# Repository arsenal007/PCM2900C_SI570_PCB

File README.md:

# PCM2900C Si570
KiCAD PCB Project of SDR processor board, based on PCM2900C and Si570

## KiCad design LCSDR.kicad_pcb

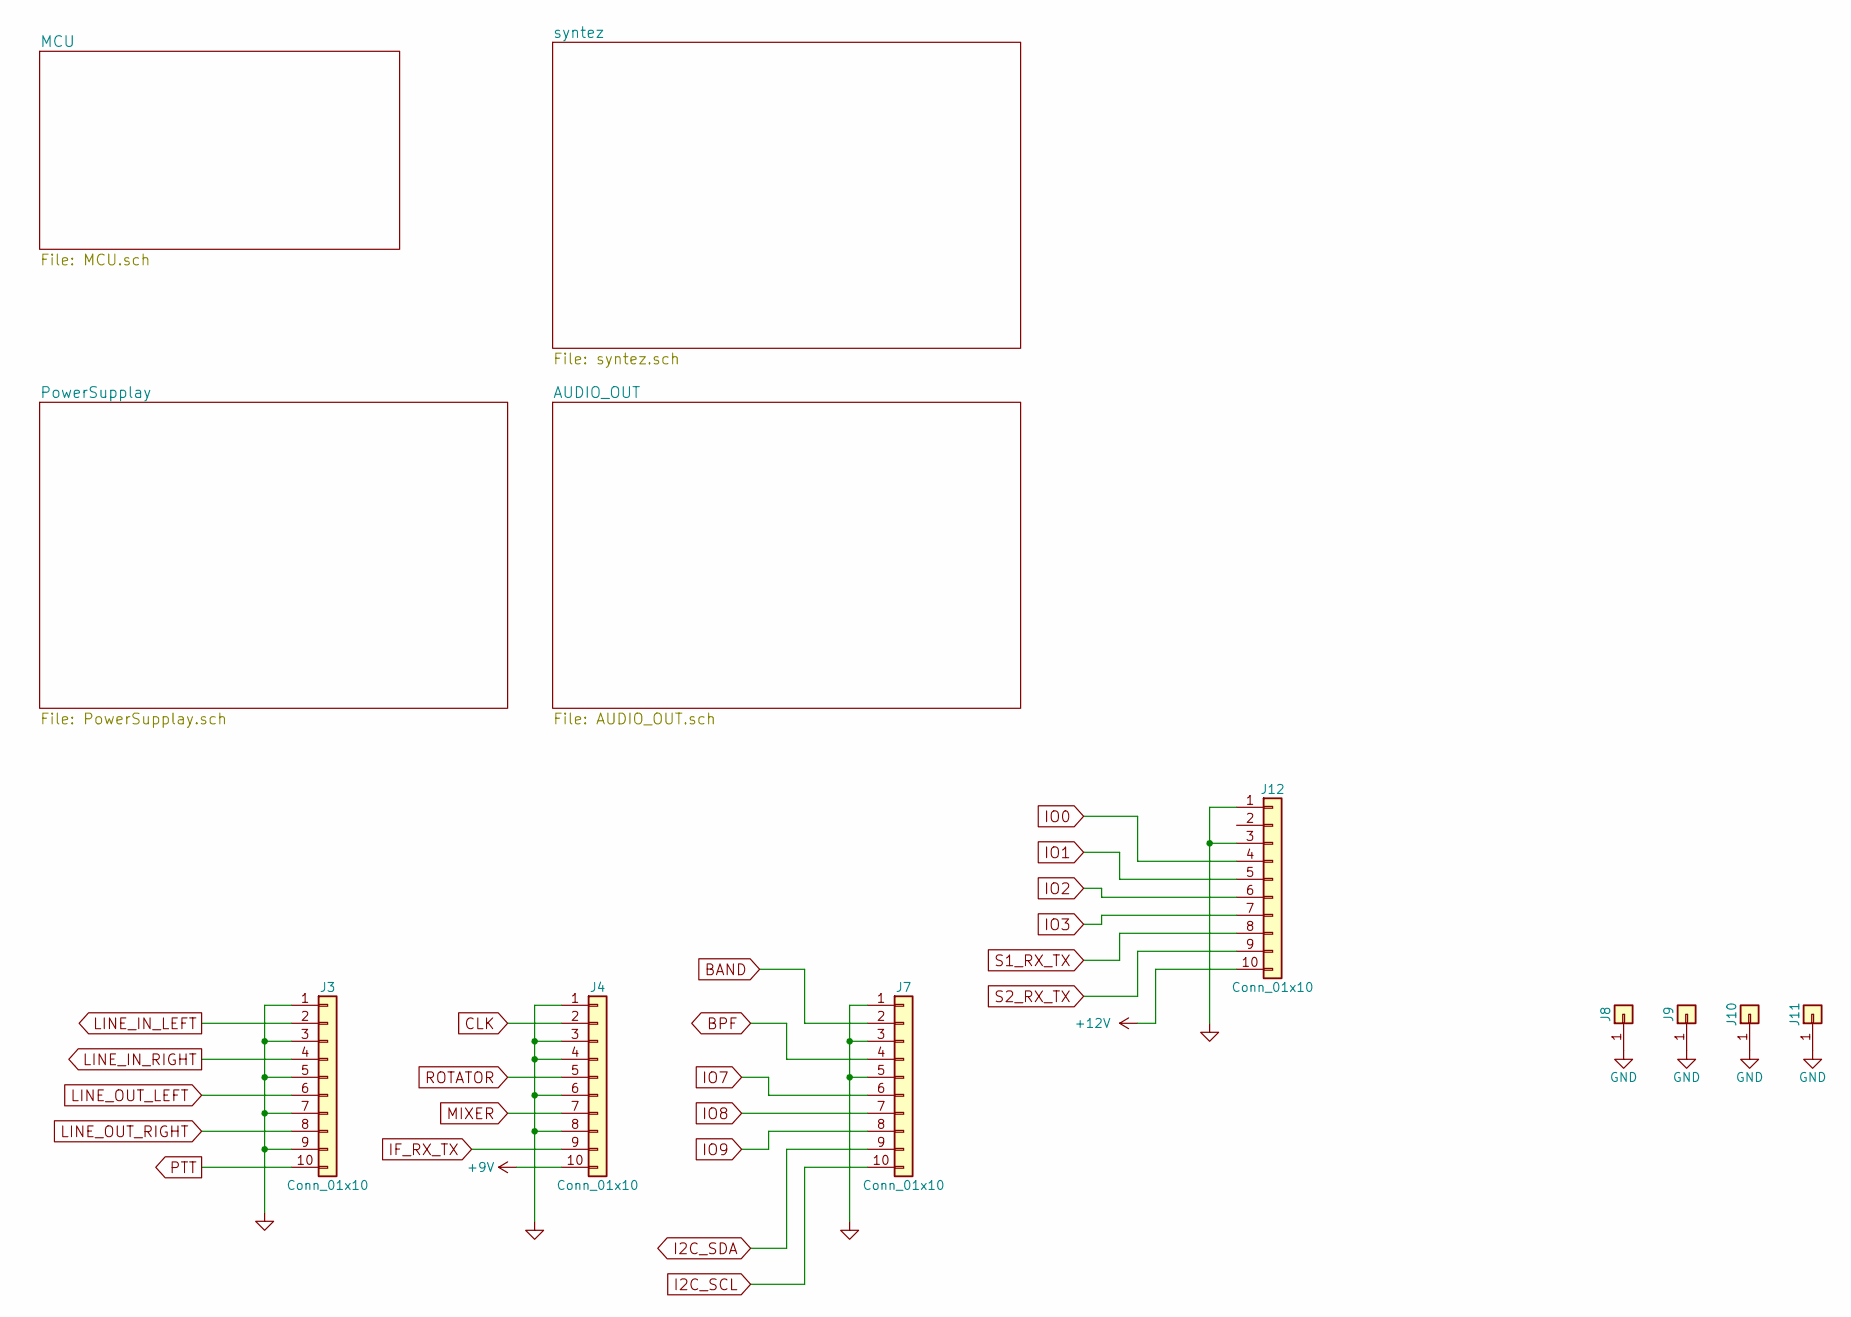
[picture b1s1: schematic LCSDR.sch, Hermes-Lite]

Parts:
J3, J4, J7, J12: Conn_01x10; Pin_Header_Straight_1x10_Pitch2.54mm
J8, J9, J10, J11: Conn_01x01; MountingHole_3.2mm_M3_DIN965_Pad

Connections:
+9V: J4.10; also elsewhere on the board
+12V: J12.10; also elsewhere on the board
BAND: J7.2; also elsewhere on the board
CLK: J4.2; also elsewhere on the board
GND: J3.1, J3.3, J3.5, J3.7, J3.9, J4.1, J4.3, J4.4, J4.6, J4.8, J7.1, J7.3, J7.5, J8.1, J9.1, J10.1, J11.1, J12.1, J12.3; also elsewhere on the board
I2C_SCL: J7.10; also elsewhere on the board
I2C_SDA: J7.9; also elsewhere on the board
IF_RX_TX: J4.9; also elsewhere on the board
IO0: J12.4; also elsewhere on the board
IO1: J12.5; also elsewhere on the board
IO2: J12.6; also elsewhere on the board
IO3: J12.7; also elsewhere on the board
IO7: J7.6; also elsewhere on the board
IO8: J7.7; also elsewhere on the board
IO9: J7.8; also elsewhere on the board
LINE_IN_LEFT: J3.2; also elsewhere on the board
LINE_IN_RIGHT: J3.4; also elsewhere on the board
LINE_OUT_LEFT: J3.6; also elsewhere on the board
LINE_OUT_RIGHT: J3.8; also elsewhere on the board
MIXER: J4.7; also elsewhere on the board
ROTATOR: J4.5; also elsewhere on the board
S1_RX_TX: J12.8; also elsewhere on the board
S2_RX_TX: J12.9; also elsewhere on the board

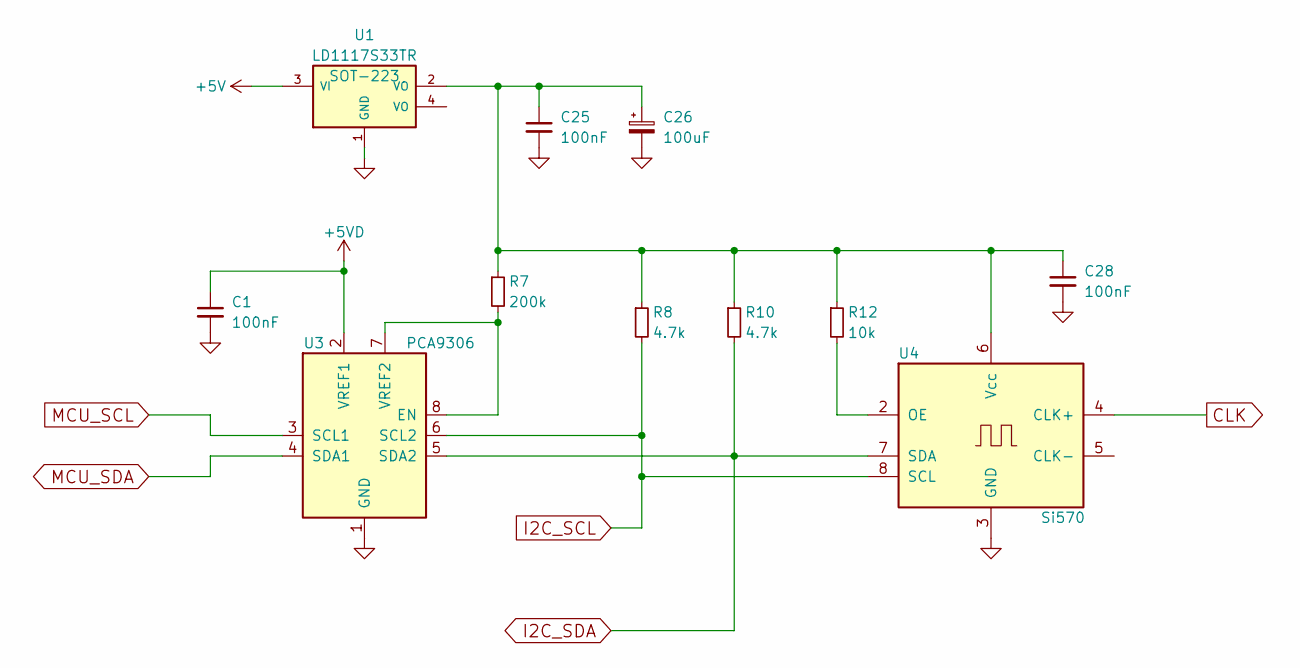
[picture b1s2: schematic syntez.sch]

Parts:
C1, C25, C28: 100nF; C_1206_0603
C26: 100uF; CP_Radial_D6.3mm_P2.50mm
R7: 200k; R_1206_0603
R8, R10: 4.7k; R_1206_0603
R12: 10k; R_1206_0603
U1: LD1117S33TR; SOT-223
U3: PCA9306; SSOP-8_2.95x2.8mm_Pitch0.65mm
U4: Si570; Oscillator_SMD_SI570_SI571_Standard

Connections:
+5V: U1.3 (VI); also elsewhere on the board
+5VD: C1.1, U3.2 (VREF1); also elsewhere on the board
CLK: U4.4 (CLK+); also elsewhere on the board
GND: C1.2, C25.2, C26.2, C28.2, U1.1 (GND), U3.1 (GND), U4.3 (GND); also elsewhere on the board
I2C_SCL: R8.2, U3.6 (SCL2), U4.8 (SCL); also elsewhere on the board
I2C_SDA: R10.2, U3.5 (SDA2), U4.7 (SDA); also elsewhere on the board
MCU_SCL: U3.3 (SCL1); also elsewhere on the board
MCU_SDA: U3.4 (SDA1); also elsewhere on the board
unnamed: C25.1, C26.1, C28.1, R7.1, R8.1, R10.1, R12.1, U1.2 (VO), U4.6 (Vcc)
unnamed: R7.2, U3.7 (VREF2), U3.8 (EN)
unnamed: R12.2, U4.2 (OE)

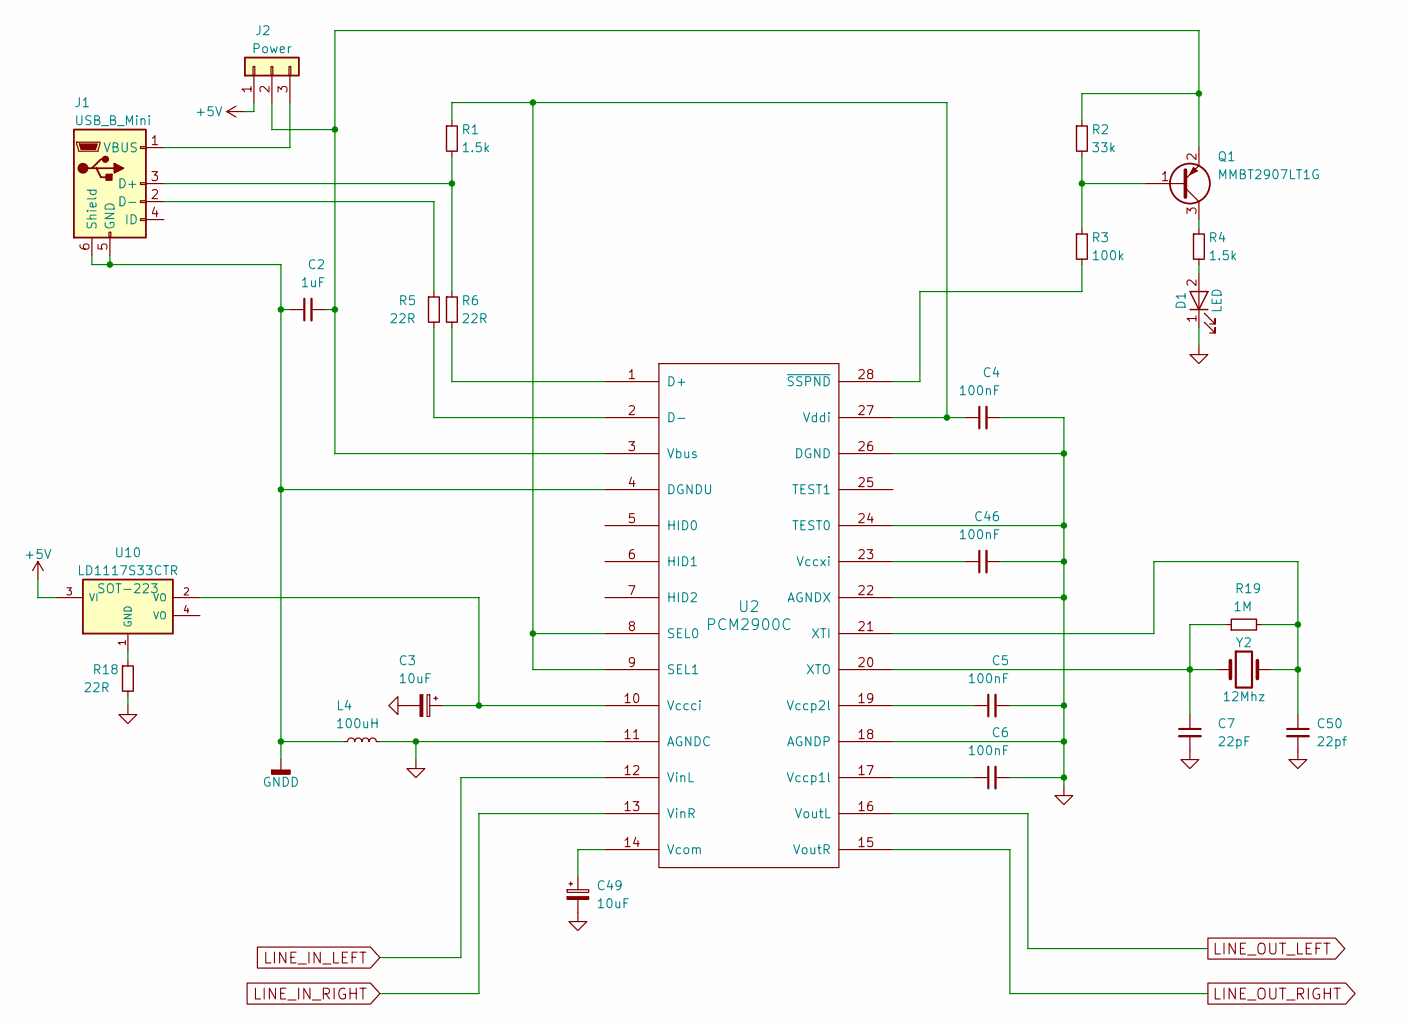
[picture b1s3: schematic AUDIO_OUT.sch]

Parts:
C2: 1uF; C_1206_0603
C3, C49: 10uF; CP_Radial_D5.0mm_P2.00mm
C4, C5, C6, C46: 100nF; C_1206_0603
C7: 22pF; C_1206_0603
C50: 22pf; C_1206_0603
D1: LED; LED_0603_HandSoldering
J1: USB_B_Mini; USB_Mini-B
J2: Power; Pin_Header_Straight_1x03_Pitch2.54mm
L4: 100uH; Choke_Horizontal_RM10mm
Q1: MMBT2907LT1G; SOT-23
R1, R4: 1.5k; R_1206_0603
R2: 33k; R_1206_0603
R3: 100k; R_1206_0603
R5, R6, R18: 22R; R_1206_0603
R19: 1M; R_1206_0603
U2: PCM2900C; SSOP-28_5.3x10.2mm_Pitch0.65mm
U10: LD1117S33CTR; SOT-223
Y2: 12Mhz; Crystal_HC49-U_Vertical

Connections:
+5V: J2.1, U10.3 (VI); also elsewhere on the board
GND: C3.2, C4.2, C5.2, C6.2, C7.2, C46.2, C49.2, C50.2, D1.1 (K), L4.2, R18.2, U2.11 (AGNDC), U2.18 (AGNDP), U2.22 (AGNDX), U2.24 (TEST0), U2.26 (DGND); also elsewhere on the board
GNDD: C2.1, J1.5 (GND), J1.6 (Shield), L4.1, U2.4 (DGNDU)
LINE_IN_LEFT: U2.12 (VinL); also elsewhere on the board
LINE_IN_RIGHT: U2.13 (VinR); also elsewhere on the board
LINE_OUT_LEFT: U2.16 (VoutL); also elsewhere on the board
LINE_OUT_RIGHT: U2.15 (VoutR); also elsewhere on the board
unnamed: C2.2, J2.2, Q1.2 (E), R2.1, U2.3 (Vbus)
unnamed: C3.1, U2.10 (Vccci), U10.2 (VO)
unnamed: C4.1, R1.1, U2.8 (SEL0), U2.9 (SEL1), U2.27 (Vddi)
unnamed: C5.1, U2.19 (Vccp2l)
unnamed: C6.1, U2.17 (Vccp1l)
unnamed: C7.1, R19.1, U2.20 (XTO), Y2.1
unnamed: C46.1, U2.23 (Vccxi)
unnamed: C49.1, U2.14 (Vcom)
unnamed: C50.1, R19.2, U2.21 (XTI), Y2.2
unnamed: D1.2 (A), R4.2
unnamed: J1.1 (VBUS), J2.3
unnamed: J1.2 (D-), R5.1
unnamed: J1.3 (D+), R1.2, R6.1
unnamed: Q1.1 (B), R2.2, R3.1
unnamed: Q1.3 (C), R4.1
unnamed: R3.2, U2.28 (~SSPND)
unnamed: R5.2, U2.2 (D-)
unnamed: R6.2, U2.1 (D+)
unnamed: R18.1, U10.1 (GND)

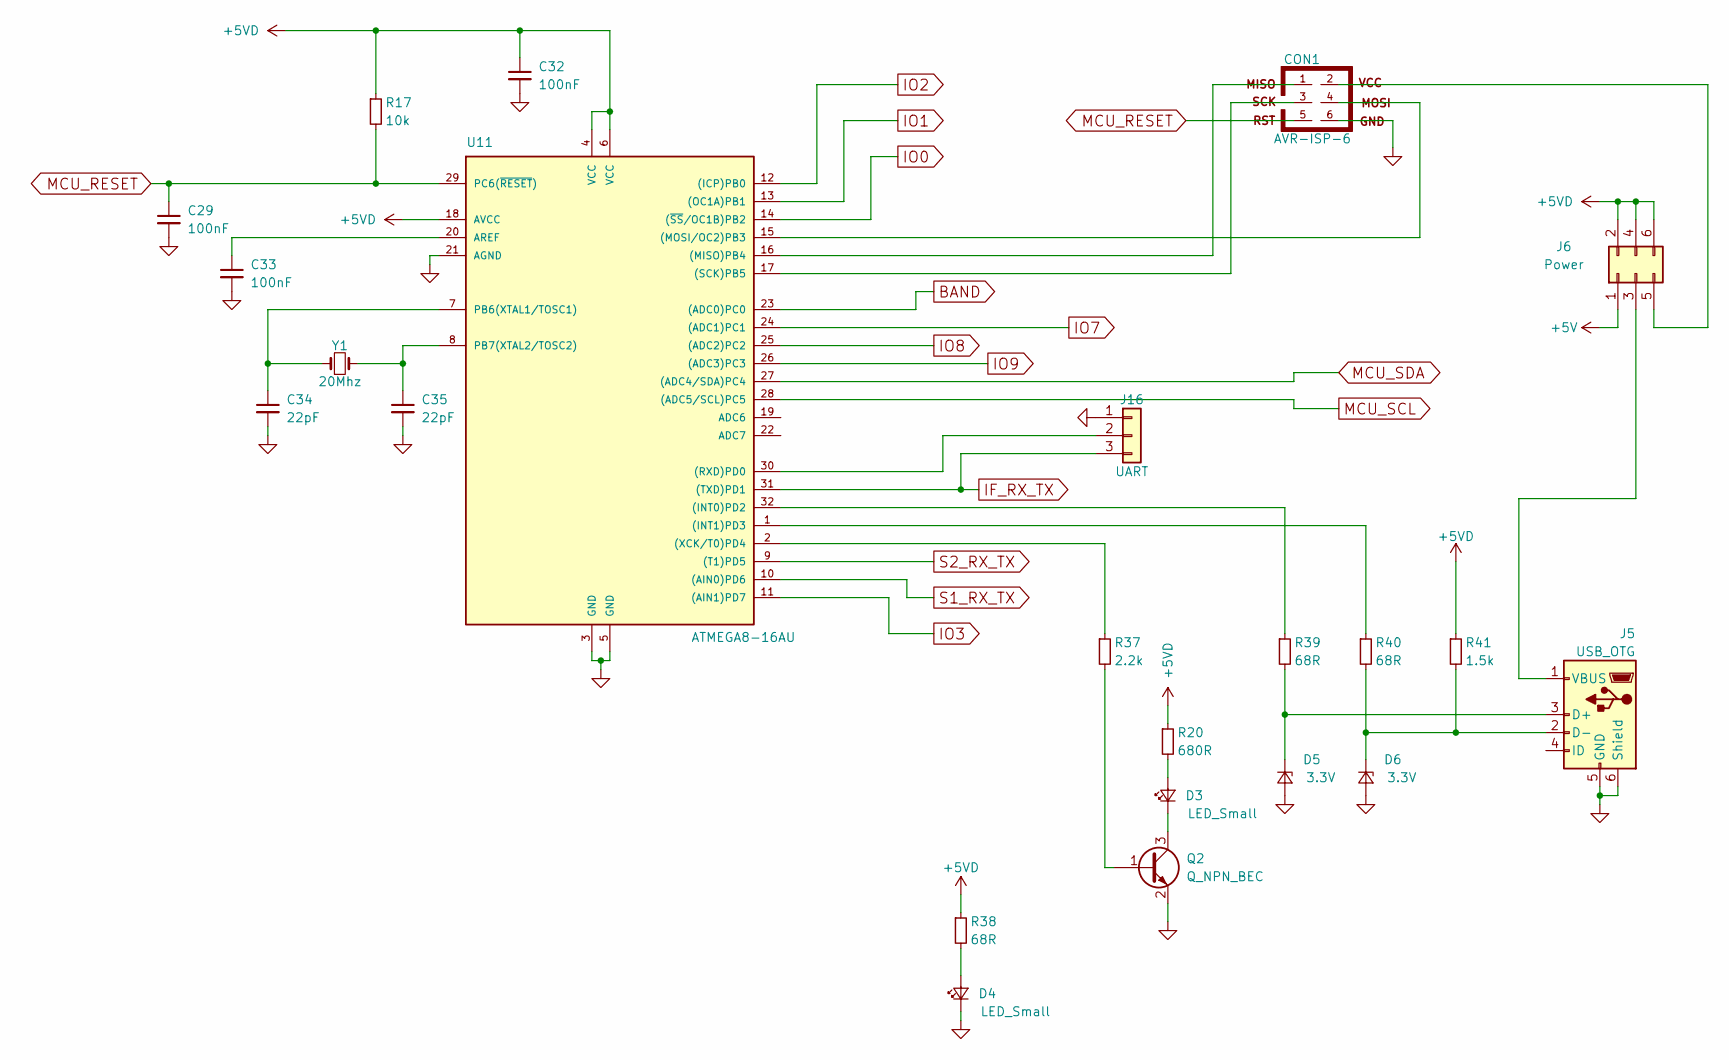
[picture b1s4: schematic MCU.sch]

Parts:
C29, C32, C33: 100nF; C_1206_0603
C34, C35: 22pF; C_1206_0603
CON1: AVR-ISP-6; Pin_Header_Straight_2x03_Pitch2.54mm
D3, D4: LED_Small; LED_0603_HandSoldering
D5, D6: 3.3V; D_MiniMELF
J5: USB_OTG; USB_Mini-B
J6: Power; Pin_Header_Straight_2x03_Pitch2.54mm
J16: UART; Pin_Header_Straight_1x03_Pitch2.54mm
Q2: Q_NPN_BEC; SOT-23
R17: 10k; R_1206_0603
R20: 680R; R_1206_0603
R37: 2.2k; R_1206_0603
R38, R39, R40: 68R; R_1206_0603
R41: 1.5k; R_1206_0603
U11: ATMEGA8-16AU; TQFP-32_7x7mm_Pitch0.8mm
Y1: 20Mhz; Crystal_HC49-U_Vertical

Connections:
+5V: J6.1; also elsewhere on the board
+5VD: C32.1, J6.2, J6.4, J6.6, R17.1, R20.1, R38.1, R41.1, U11.4 (VCC), U11.6 (VCC), U11.18 (AVCC); also elsewhere on the board
BAND: U11.23 ((ADC0)PC0); also elsewhere on the board
GND: C29.2, C32.2, C33.2, C34.2, C35.2, CON1.6, D4.1 (K), D5.2 (A), D6.2 (A), J5.5 (GND), J5.6 (Shield), J16.1, Q2.2 (E), U11.3 (GND), U11.5 (GND), U11.21 (AGND); also elsewhere on the board
IF_RX_TX: J16.3, U11.31 ((TXD)PD1); also elsewhere on the board
IO0: U11.14 ((~SS~/OC1B)PB2); also elsewhere on the board
IO1: U11.13 ((OC1A)PB1); also elsewhere on the board
IO2: U11.12 ((ICP)PB0); also elsewhere on the board
IO3: U11.11 ((AIN1)PD7); also elsewhere on the board
IO7: U11.24 ((ADC1)PC1); also elsewhere on the board
IO8: U11.25 ((ADC2)PC2); also elsewhere on the board
IO9: U11.26 ((ADC3)PC3); also elsewhere on the board
MCU_RESET: C29.1, CON1.5, R17.2, U11.29 (PC6(~RESET~))
MCU_SCL: U11.28 ((ADC5/SCL)PC5); also elsewhere on the board
MCU_SDA: U11.27 ((ADC4/SDA)PC4); also elsewhere on the board
unnamed: C33.1, U11.20 (AREF)
unnamed: C34.1, U11.7 (PB6(XTAL1/TOSC1)), Y1.1
unnamed: C35.1, U11.8 (PB7(XTAL2/TOSC2)), Y1.2
unnamed: CON1.1, U11.16 ((MISO)PB4)
unnamed: CON1.2, J6.5
unnamed: CON1.3, U11.17 ((SCK)PB5)
unnamed: CON1.4, U11.15 ((MOSI/OC2)PB3)
unnamed: D3.1 (K), Q2.3 (C)
unnamed: D3.2 (A), R20.2
unnamed: D4.2 (A), R38.2
unnamed: D5.1 (K), J5.3 (D+), R39.2
unnamed: D6.1 (K), J5.2 (D-), R40.2, R41.2
unnamed: J5.1 (VBUS), J6.3
unnamed: J16.2, U11.30 ((RXD)PD0)
unnamed: Q2.1 (B), R37.2
unnamed: R37.1, U11.2 ((XCK/T0)PD4)
unnamed: R39.1, U11.32 ((INT0)PD2)
unnamed: R40.1, U11.1 ((INT1)PD3)
S1_RX_TX: U11.10 ((AIN0)PD6); also elsewhere on the board
S2_RX_TX: U11.9 ((T1)PD5); also elsewhere on the board

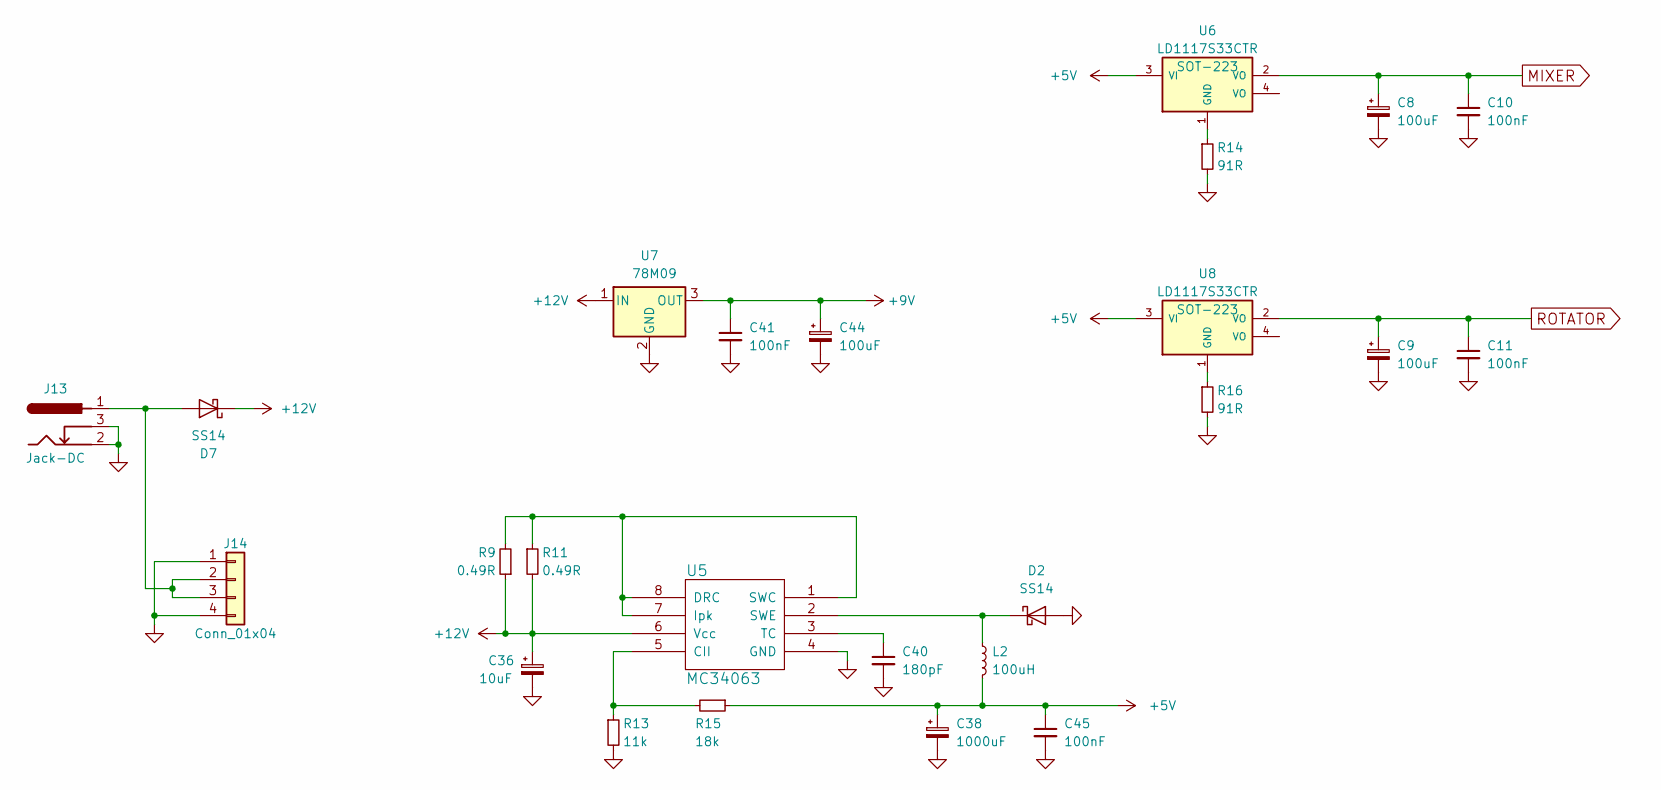
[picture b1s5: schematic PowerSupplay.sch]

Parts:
C8, C9, C44: 100uF; CP_Radial_D6.3mm_P2.50mm
C10, C11, C41, C45: 100nF; C_1206_0603
C36: 10uF; CP_Radial_D6.3mm_P2.50mm
C38: 1000uF; CP_Radial_D10.0mm_P5.00mm
C40: 180pF; C_1206_0603
D2: SS14; D_SMA_Handsoldering
D7: SS14; D_DO-41_SOD81_P10.16mm_Horizontal
J13: Jack-DC; BARREL_JACK
J14: Conn_01x04; Pin_Header_Straight_1x04_Pitch2.54mm
L2: 100uH; Choke_Toroid_5x10mm_Vertical
R9, R11: 0.49R; R_Axial_DIN0207_L6.3mm_D2.5mm_P10.16mm_Horizontal
R13: 11k; R_1206_0603
R14, R16: 91R; R_1206_0603
R15: 18k; R_1206_0603
U5: MC34063; SOIC-8_3.9x4.9mm_Pitch1.27mm
U6, U8: LD1117S33CTR; SOT-223
U7: 78M09; TO-252-2_Rectifier

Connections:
+5V: C38.1, C45.1, L2.2, R15.1, U6.3 (VI), U8.3 (VI); also elsewhere on the board
+9V: C41.1, C44.1, U7.3 (OUT); also elsewhere on the board
+12V: C36.1, D7.1 (K), R9.1, R11.2, U5.6 (Vcc), U7.1 (IN); also elsewhere on the board
GND: C8.2, C9.2, C10.2, C11.2, C36.2, C38.2, C40.2, C41.2, C44.2, C45.2, D2.2 (A), J13.2, J13.3, J14.1, J14.4, R13.2, R14.2, R16.2, U5.4 (GND), U7.2 (GND); also elsewhere on the board
MIXER: C8.1, C10.1, U6.2 (VO); also elsewhere on the board
unnamed: C40.1, U5.3 (TC)
unnamed: D2.1 (K), L2.1, U5.2 (SWE)
unnamed: D7.2 (A), J13.1, J14.2, J14.3
unnamed: R9.2, R11.1, U5.1 (SWC), U5.7 (Ipk), U5.8 (DRC)
unnamed: R13.1, R15.2, U5.5 (CII)
unnamed: R14.1, U6.1 (GND)
unnamed: R16.1, U8.1 (GND)
ROTATOR: C9.1, C11.1, U8.2 (VO); also elsewhere on the board

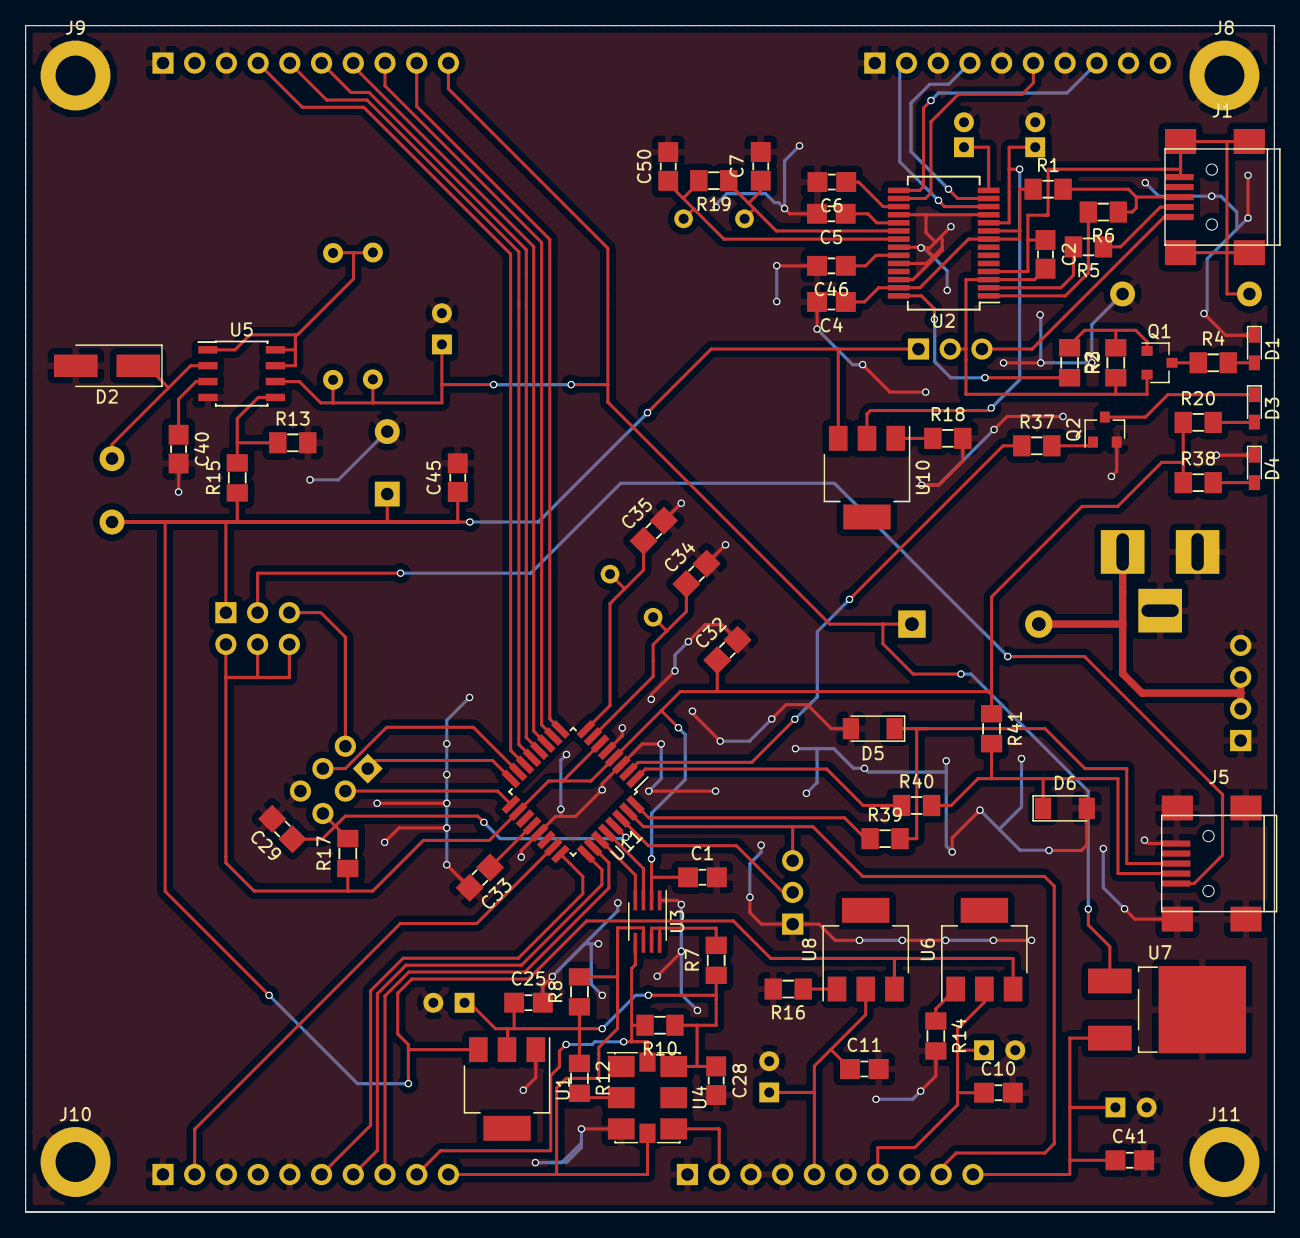
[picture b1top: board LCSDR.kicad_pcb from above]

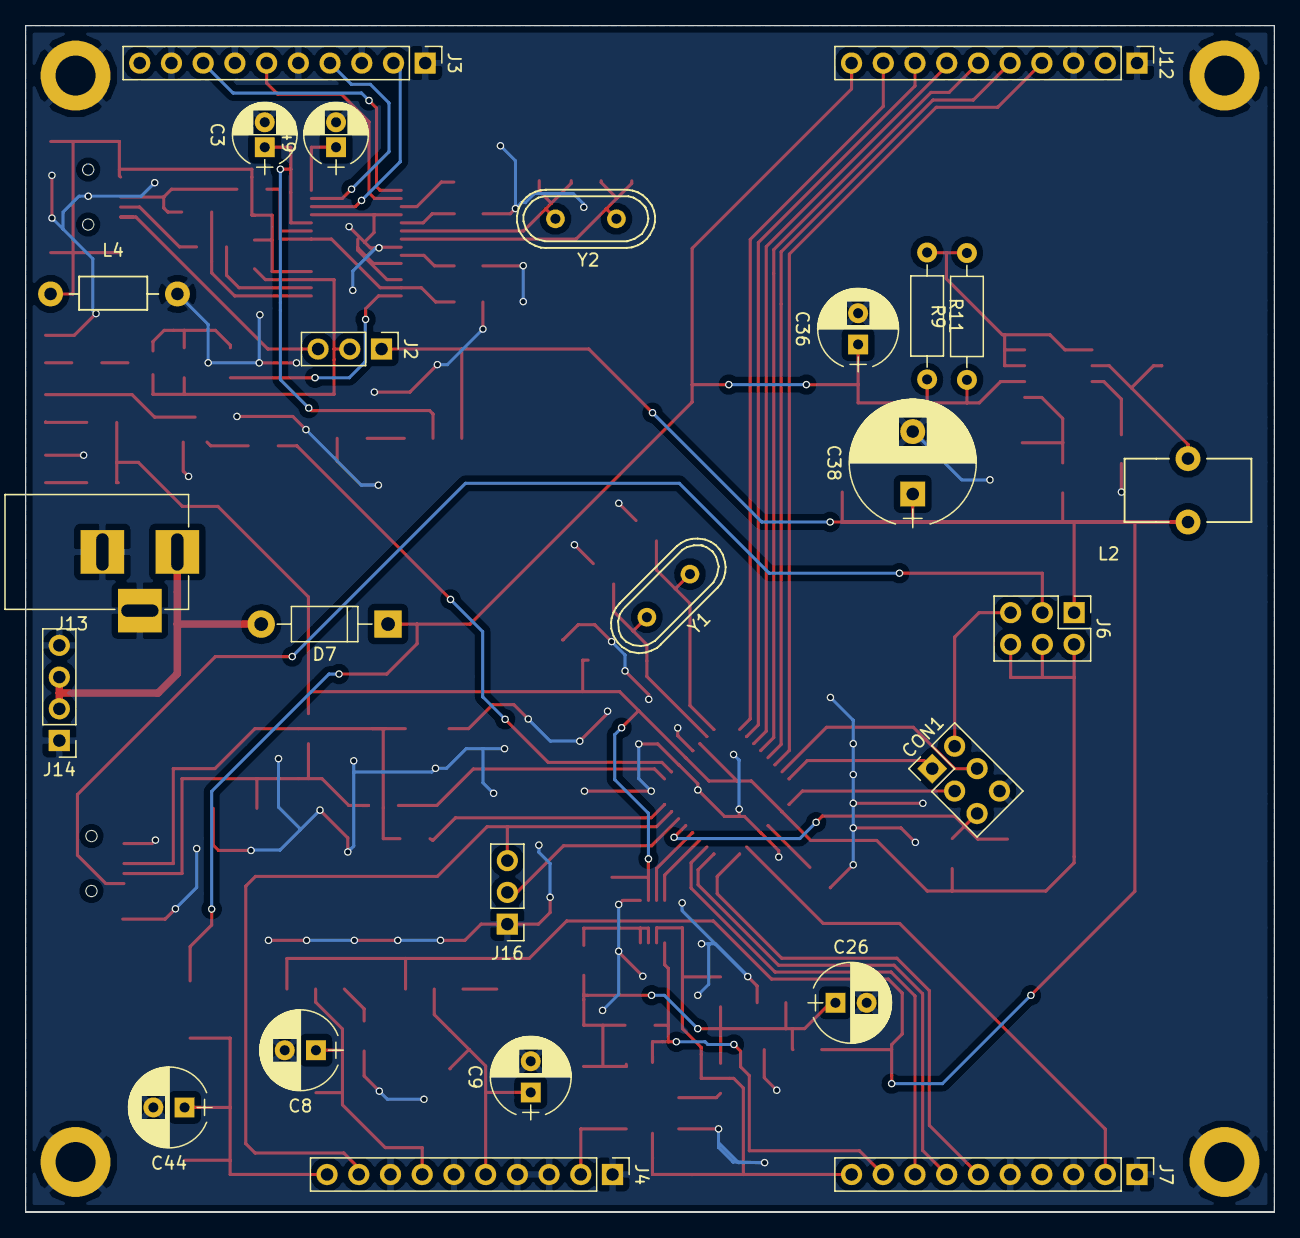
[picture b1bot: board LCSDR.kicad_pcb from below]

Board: 2 copper layers, 100.0 x 95.0 mm, 92 parts (25 on the bottom side), 76 nets.

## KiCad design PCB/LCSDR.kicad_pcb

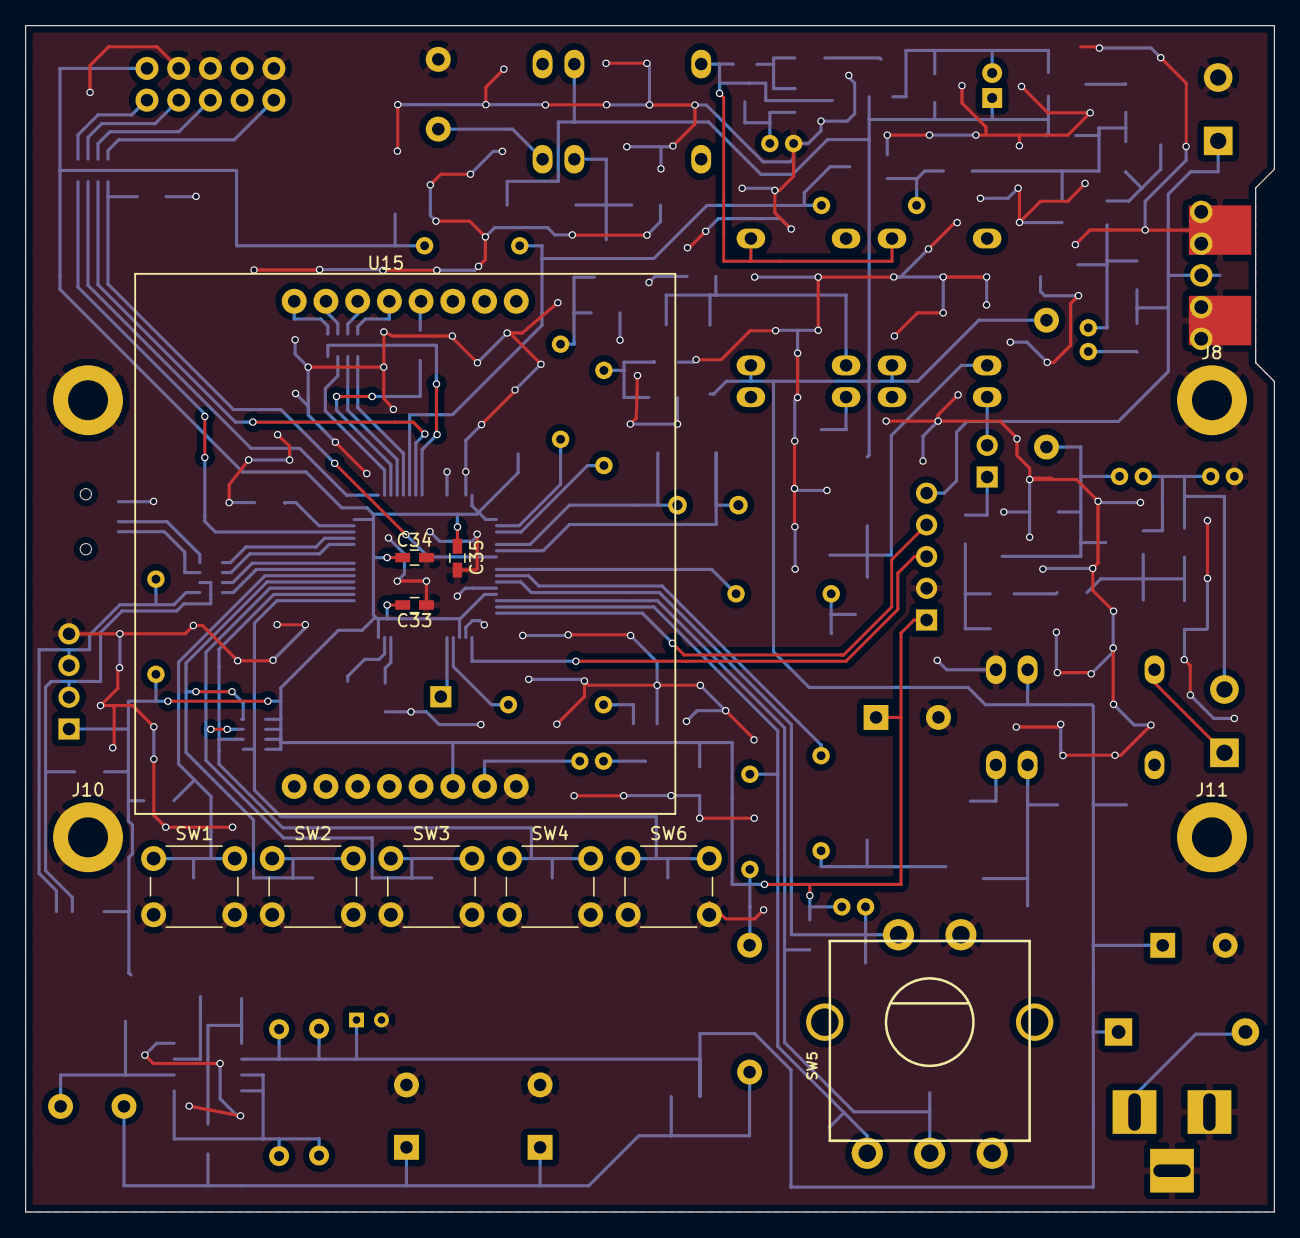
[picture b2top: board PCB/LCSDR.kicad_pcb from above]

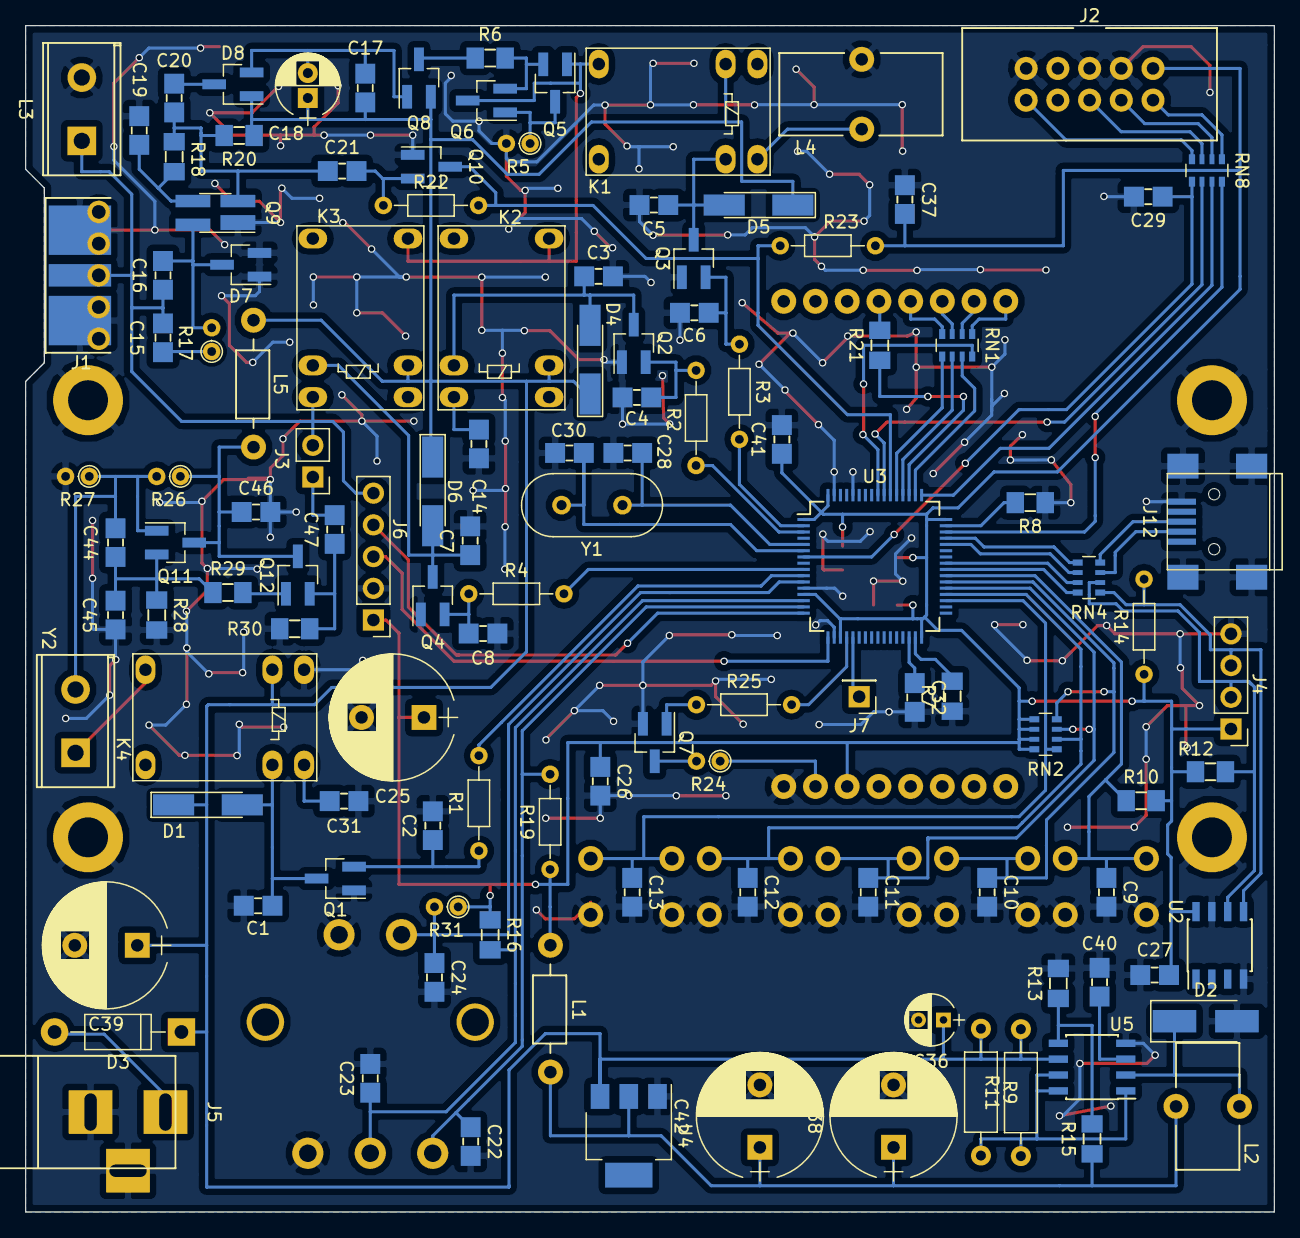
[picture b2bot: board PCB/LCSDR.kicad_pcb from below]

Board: 2 copper layers, 100.0 x 95.0 mm, 135 parts (121 on the bottom side), 90 nets.

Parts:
C1, C2, C3, C4, C5, C6, C7, C8, C9, C10, C11, C12, C13, C15, C17, C19, C20, C21, C22, C23, C24, C26, C27, C29, C32, C37, C41, C46, C47: 100nF; C_1206_0603
C14, C44, C45: 100pF; C_1206_0603
C16: 13; C_1206_0603
C18: 10uF; CP_Radial_D5.0mm_P2.00mm
C25: 330uF; CP_Radial_D10.0mm_P5.00mm
C28, C30: 22; C_1206_0603
C31: 33pF; C_1206_0603
C33, C34, C35: 100nF; C_0603_HandSoldering
C36: 10uF; CP_Radial_D4.0mm_P2.00mm
C38, C39, C42: 1000uF; CP_Radial_D10.0mm_P5.00mm
C40: 200pF; C_1206_0603
D1, D4, D5, D6: LL4148; D_MiniMELF_Handsoldering
D2: SS14; D_SMA_Handsoldering
D3: SS14; D_DO-41_SOD81_P10.16mm_Horizontal
D7, D8: BAV99; SOT-23_Handsoldering
J1: F; RFCONNECTOR
J2: IDC10 Serial Wire; USBBLASTER
J3: LC/G3UUR; Pin_Header_Straight_1x02_Pitch2.54mm
J4: Conn_01x04; Pin_Header_Straight_1x04_Pitch2.54mm
J5: Jack-DC; BARREL_JACK
J6: NEO-7M; Pin_Header_Straight_1x05_Pitch2.54mm
J7: Conn_01x01; Pin_Header_Straight_1x01_Pitch2.54mm
J8, J9, J10, J11: Conn_01x01; MountingHole_3.2mm_M3_DIN965_Pad
J12: USB_B_Mini; USB_Mini-B
K1, K2, K3, K4: TIANBO-HJR-4102-L; Relay_SPDT_HJR-4102
L1: 280uH; Choke_Horizontal_RM10mm
L2: 19uH; Choke_Toroid_5x10mm_Vertical
L3: Terminal; TerminalBlock_DG306-5.0_2pol
L4: 8uH; Choke_Toroid_6,5x13mm_Vertical
L5: 100uH; Choke_Horizontal_RM10mm
Q1, Q2, Q3, Q4: MMBT2222; SOT-23_Handsoldering
Q5, Q6: BFT92; SOT-23_Handsoldering
Q7: BC817; SOT-23_Handsoldering
Q8: BC857; SOT-23_Handsoldering
Q9: BF998; SOT-143_Handsoldering
Q10, Q11, Q12: SS9018; SOT-23_Handsoldering
R1, R2, R3, R4: 2.7k; R_Axial_DIN0204_L3.6mm_D1.6mm_P7.62mm_Horizontal
R5: 10; R_Axial_DIN0204_L3.6mm_D1.6mm_P1.90mm_Vertical
R6, R28, R29, R30: 1k; R_1206_0603
R7, R8: 0*; R_1206_0603
R9, R11: 0.49R; R_Axial_DIN0207_L6.3mm_D2.5mm_P10.16mm_Horizontal
R10, R21: 56R; R_1206_0603
R12: 2.7k; R_1206_0603
R13: 11k; R_1206_0603
R14, R19: 4.7k; R_Axial_DIN0204_L3.6mm_D1.6mm_P7.62mm_Horizontal
R15: 18k; R_1206_0603
R16: 4.7k; R_1206_0603
R17: 1k; R_Axial_DIN0204_L3.6mm_D1.6mm_P1.90mm_Vertical
R18: 10k; R_1206_0603
R20: 330; R_1206_0603
R22: 47k; R_Axial_DIN0204_L3.6mm_D1.6mm_P7.62mm_Horizontal
R23: 470; R_Axial_DIN0204_L3.6mm_D1.6mm_P7.62mm_Horizontal
R24: 56R; R_Axial_DIN0204_L3.6mm_D1.6mm_P1.90mm_Vertical
R25: 56R; R_Axial_DIN0204_L3.6mm_D1.6mm_P7.62mm_Horizontal
R26: 100k; R_Axial_DIN0204_L3.6mm_D1.6mm_P1.90mm_Vertical
R27: 47k; R_Axial_DIN0204_L3.6mm_D1.6mm_P1.90mm_Vertical
R31: 4.7k; R_Axial_DIN0204_L3.6mm_D1.6mm_P1.90mm_Vertical
RN1: 56R; R_Array_Convex_4x0603
RN2: 4.7k; R_Array_Convex_4x0603
RN4, RN8: 47; R_Array_Convex_4x0603
SW1, SW2, SW3, SW4, SW6: SW_Push_Dual; SW_PUSH_6mm_h13mm
SW5: ENCODER; SF-ROTARY-ENCODER
U2: FM24CL16B; SOIC-8_3.9x4.9mm_Pitch1.27mm
U3: STM32F401RCTx; LQFP-64_10x10mm_Pitch0.5mm
U4: AP1117-33; SOT-223
U5: MC34063; SOIC-8_3.9x4.9mm_Pitch1.27mm
U15: Nokia_5110_LCD; Nokia_5110-3310_LCD
Y1: 20Mhz; Crystal_HC49-U_Vertical
Y2: Crystal; TerminalBlock_DG306-5.0_2pol

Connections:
+3V3: C25.1, C26.1, C27.1, C33.2, C34.2, C35.2, C37.2, C41.1, J2.1, J4.1, J6.1, L1.2, R10.2, R12.1, R14.1, R16.1, R19.1, R23.1, R31.1, RN2.5, RN2.6, RN2.7, RN2.8, U2.8, U3.1, U3.13, U3.19, U3.32, U3.48, U3.64, U15.6
+12V: C17.1, C18.1, C36.1, C39.1, D1.1, D3.1, D4.1, D5.1, D6.1, D8.1, K1.8, K2.8, K3.8, K4.8, L5.2, Q8.2, R9.1, R11.2, R20.1, U4.3, U5.6
ADC: J7.1, U3.21
ENCODER_A: C23.1, R16.2, SW5.2, U3.14
ENCODER_B: C22.1, R19.2, SW5.1, U3.15
F_LC: Q10.3, R22.2, R23.2, U3.54
F_Q: C15.1, C16.1, J1.1, J3.2, J6.5, K3.6, L3.1
GND: C1.2, C2.2, C3.2, C4.2, C5.2, C6.2, C7.2, C8.2, C9.2, C10.2, C11.2, C12.2, C13.2, C14.2, C19.1, C22.2, C23.2, C24.2, C25.2, C26.2, C27.2, C28.2, C29.2, C30.2, C31.2, C32.2, C33.1, C34.1, C35.1, C36.2, C37.1, C38.2, C39.2, C40.2, C41.2, C42.2, C45.2, C46.2, D2.2, D7.1, D7.2, J1.2, J2.3, J2.5, J2.9, J4.4, J5.2, J5.3, J6.2, J8.1, J9.1, J10.1, J11.1, J12.5, J12.6, K4.7, L3.2, L4.2, Q1.1, Q2.1, Q3.1, Q4.1, Q7.2, Q9.1, Q10.1, R5.2, R7.1, R8.2, R13.2, R27.2, R28.2, R30.2, SW1.2, SW2.2, SW3.2, SW4.2, SW5.3, SW5.5, SW6.2, U2.4, U2.7, U3.12, U3.18, U3.60, U3.63, U4.1, U5.4, U15.8
I2C_SCL: J4.2, R12.2, RN4.2, U2.6
I2C_SCL_MCU: RN4.7, U3.41
I2C_SDA: J4.3, R14.2, RN4.1, U2.5
I2C_SDA_MCU: RN4.8, U3.40
KEY_A: C9.1, R10.1, SW1.1, U3.39
KEY_B: C10.1, RN2.4, SW2.1, U3.38
KEY_C: C11.1, RN2.3, SW3.1, U3.37
KEY_D: C12.1, RN2.2, SW4.1, U3.36
KEY_E: C13.1, RN2.1, SW6.1, U3.35
KEY_MENU: C24.1, R31.2, SW5.4, U3.11
LCD_CE: RN1.7, U3.50
LCD_CLK: R21.1, U3.51
LCD_DC: RN1.6, U3.52
LCD_DIN: RN1.5, U3.53
LCD_LIGHT: R25.2, U3.20
LCD_RESET: RN1.8, U3.56
MCU_RESET: C29.1, RN8.5, U3.7
unnamed: C2.1, Q1.2, R1.1
unnamed: C4.1, Q2.2, R2.1
unnamed: C6.1, Q3.2, R3.1
unnamed: C8.1, Q4.2, R4.1
unnamed: C14.1, K2.6
unnamed: C15.2, R17.1
unnamed: C16.2, D7.3, Q9.4, R17.2
unnamed: C17.2, C18.2, D8.2, Q8.1
unnamed: C19.2, Q9.3, R18.2
unnamed: C20.1, D8.3
unnamed: C20.2, C21.1, Q9.2, R18.1, R20.2
unnamed: C21.2, Q10.2, R22.1
unnamed: C28.1, U3.5, Y1.1
unnamed: C30.1, U3.6, Y1.2
unnamed: C31.1, K4.6
unnamed: C32.1, U3.30
unnamed: C38.1, C42.1, L1.1, L2.2, R15.1, U4.2
unnamed: C40.1, U5.3
unnamed: C44.1, Q11.1, R26.2, R27.1, Y2.2
unnamed: C44.2, C45.1, Q11.2, R28.1, R29.1
unnamed: C46.1, L5.1, Q11.3, Q12.3, R26.1
unnamed: C47.1, Q12.2, R30.1
unnamed: C47.2, J3.1
unnamed: D2.1, L2.1, U5.2
unnamed: D3.2, J5.1
unnamed: J2.2, RN8.1
unnamed: J2.4, RN8.2
unnamed: J2.6, RN8.3
unnamed: J2.10, RN8.4
unnamed: J12.2, RN4.3
unnamed: J12.3, RN4.4
unnamed: K1.6, L4.1
unnamed: K1.12, K2.12, K3.12, Q5.1, Q6.3
unnamed: K4.12, Y2.1
unnamed: Q5.2, Q6.2, R6.2
unnamed: Q5.3, Q6.1, R5.1
unnamed: Q7.1, R25.1
unnamed: Q7.3, R24.2
unnamed: Q8.3, R6.1
unnamed: Q12.1, R29.2
unnamed: R7.2, U3.31
unnamed: R8.1, U3.47
unnamed: R9.2, R11.1, U5.1, U5.7, U5.8
unnamed: R13.1, R15.2, U5.5
unnamed: R21.2, U15.5
unnamed: R24.1, U15.7
unnamed: RN1.1, U15.1
unnamed: RN1.2, U15.2
unnamed: RN1.3, U15.3
unnamed: RN1.4, U15.4
REL_0: C7.1, D6.2, K3.5, Q4.3
REL_0_MCU: R4.2, U3.9
REL_1: C3.1, D4.2, K2.5, Q2.3
REL_1_MCU: R2.2, U3.3
REL_2: C5.1, D5.2, K1.5, Q3.3
REL_2_MCU: R3.2, U3.2
REL_3: C1.1, D1.2, K4.5, Q1.3
REL_3_MCU: R1.2, U3.10
SWCLK: RN8.7, U3.49
SWDIO: RN8.8, U3.46
SWO: RN8.6, U3.55
USART_RX: J6.3, U3.17
USART_TX: J6.4, U3.16
USB_DM: RN4.6, U3.44
USB_DP: RN4.5, U3.45

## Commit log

2019-12-23 first commit, add first PCB
2020-07-03 production
